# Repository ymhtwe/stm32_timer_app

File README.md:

# stm32_timer_app
general purpose control applications using stm32 timer module

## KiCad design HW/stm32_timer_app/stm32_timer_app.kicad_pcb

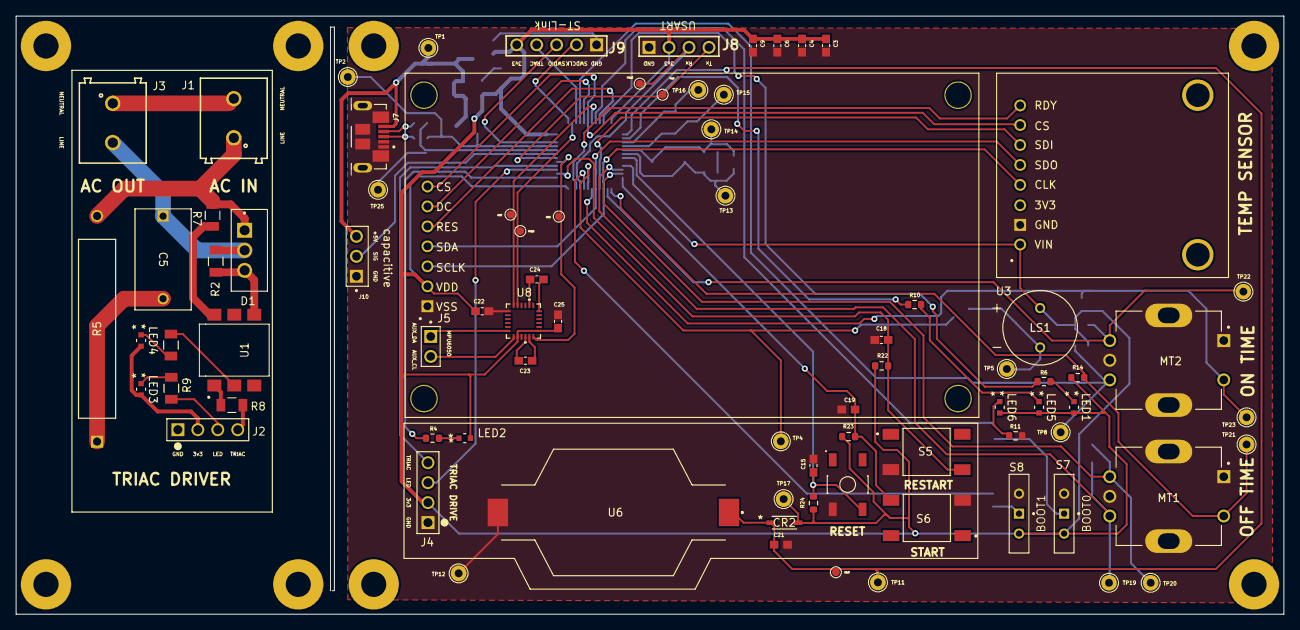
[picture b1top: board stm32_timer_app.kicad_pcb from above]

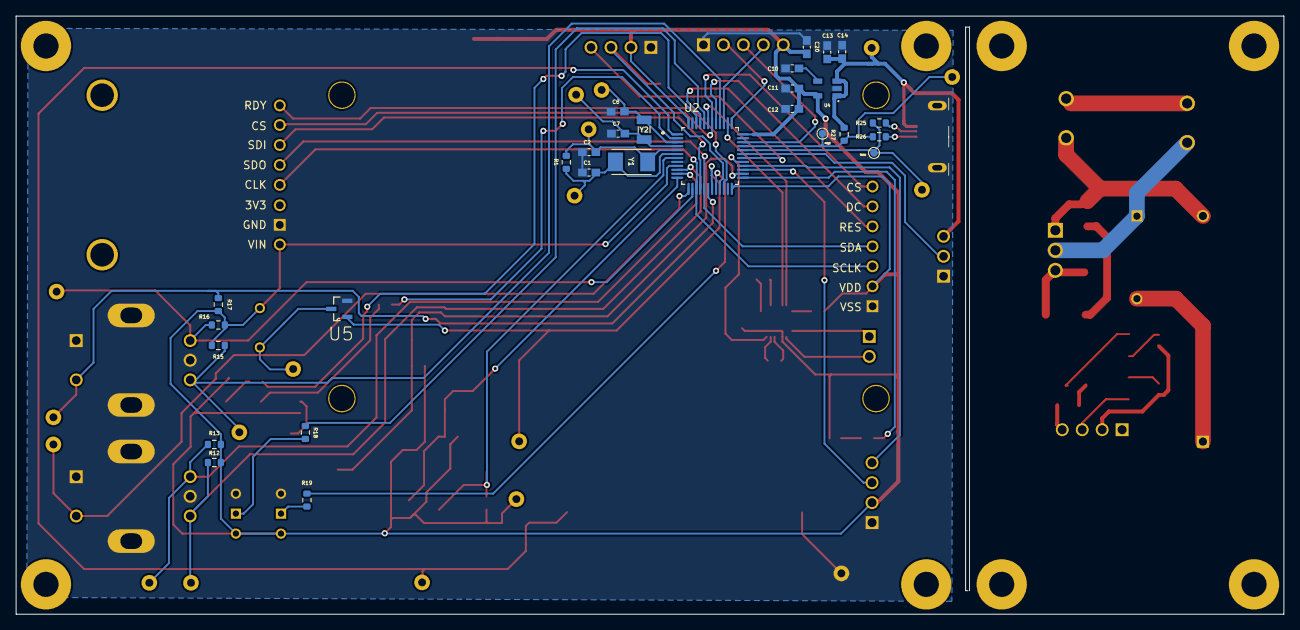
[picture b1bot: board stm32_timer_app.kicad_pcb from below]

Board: 2 copper layers, 161.3 x 76.1 mm, 101 parts (26 on the bottom side), 71 nets.

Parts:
C1, C2, C7, C8: 20p; CAPC1608X90
C3, C4, C6, C9, C12, C14, C20, C23, C25: 104; CAPC1608X90
C5: ECW-FD2J273KQ; CAP_ECWFD_FORMINGQ_12.6LX06.9TX09.9H_PAN
C10: 223; CAPC1608X90
C11: 106; CAPC1608X90
C13, C15, C18, C19: 105; CAPC1608X90
C21: LD03ZD475MAB2A; CAPC1608X90
C22, C24: 103; CAPC1608X90
CR2: 1N4148W-13-F; SOD123_DIO
D1: BTA16-600B; TO255P1040X460X1975-3
DS1: AOM12864A0-1.54WW-ANO; LCD_AOM12864A0-1.54WW-ANO
J1, J3: 691213710002
J2, J4: 61300411121; CONN_61300411121_WRE
J5: 54101-G0502LF; AMPHENOL_54101-G0502LF
J7: 105164-0001; MOLEX_105164-0001
J8: PH1RB-04-UA; HDRRA4W64P0X254_1X4_1016X250X850P
J9: PH1RB-05-UA_TEMP.; HDRRA5W64P0X254_1X5_1270X250X288P
J10: 75160-196-03LF; AMPHENOL_75160-196-03LF
LED1, LED2, LED3, LED4, LED5, LED6: 150060GS75000; LED_150060GS75000_WRE
LS1: AI-1027-TWT-3V-R; XDCR_AI-1027-TWT-3V-R
MT1, MT2: PEC11R-4215F-S0024; XDCR_PEC11R-4215F-S0024
R1, R25, R26, R27: 20R; R_0603_1608Metric
R2, R7, R9, R20: 330; RC1206N_YAG
R4, R6, R10, R11, R22, R23, R24: 330; R_0603_1608Metric
R5: 39; RES_OY_OHM
R8: 1k; RC1206N_YAG
R12, R13, R14, R15, R16, R17: 10K; R_0603_1608Metric
R18, R19: 100K; R_0603_1608Metric
S4: TL3342F160QG; SW_TL3342F160QG
S5, S6: 1571527-1; SW_1571527-1
S7, S8: MSS-102559-14A-D; SW_MSS-102559-14A-D
TP1, TP2, TP4, TP5, TP8, TP11, TP12, TP13, TP14, TP15, TP16, TP17, TP19, TP20, TP21, TP22, TP23, TP25: TestPoint_Probe; TestPoint_THTPad_D2.0mm_Drill1.0mm
U1: MOC3041SM; OPTO_MOC3041SM
U2: STM32F303C8T6; QFP50P900X900X160-48N
U3: MAX31865 AMPLIFIER; MAX31865
U4: RT9193-33GB; SOT94P279X129-5N
U5: MMBT2222A-7-F; SOT103P240X110-3N
U6: SMTU2032-LF; SMTU2032LF
U8: MPU-6050; QFN24_4X4X0P9_IVS
Y1: ABM3-8.000MHZ-J4Q-T; XTAL_ABM3-8.000MHZ-J4Q-T
Y2: ABS07-32.768KHZ-T; XTAL_ABS07-32.768KHZ-T

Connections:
/+3.3V: C3.1, C4.1, C6.1, C9.1, C11.2, C12.2, C20.1, C22.2, C25.1, CR2.2, DS1.2 (VCC), J4.2, J8.2, J9.5, LED1.2, LED2.2, LED5.2, LED6.2, LS1.P, R12.2, R13.2, R14.2, R15.2, R16.2, R17.2, R22.2, R23.2, R24.2, S7.2, S8.2, TP17.1, U2.9 (VDDA), U2.24 (VDD_1), U2.36 (VDD_2), U2.48 (VDD_3), U3.1 (VIN), U4.5 (VOUT), U8.8 (VLOGIC), U8.13 (VDD)
/+3.3VT: J2.2, LED3.2, LED4.2
/+5V: C13.2, C14.2, J7.5 (Vbus), J10.3, R27.1, TP1.1, U4.1 (VIN), U4.3 (EN)
/AUX_CL: J5.A2, U8.7 (AUX_CL)
/AUX_DA: J5.A1, U8.6 (AUX_DA)
/BOOT0: R18.2, U2.44 (BOOT0)
/BOOT1: R19.2, U2.20 (PB2)
/LED: J2.3, R9.1
/OSCIN: C2.2, R1.1, TP14.1, U2.5 (PF0/OSC_IN), Y1.1
/OSCOUT: C1.2, R1.2, TP13.1, U2.6 (PF1/OSC_OUT), Y1.2
/PA0: MT1.B, R12.1, TP19.1, U2.10 (PA0)
/PA1: MT1.A, R13.1, TP20.1, U2.11 (PA1)
/PA2: C19.1, R23.1, S6.4, U2.12 (PA2)
/PA3: MT1.2, R14.1, TP21.1, U2.13 (PA3)
/PA4: MT2.A, R16.1, TP22.1, U2.14 (PA4)
/PA5: DS1.3 (SCK), U2.15 (PA5), U3.4 (CLK)
/PA6: U2.16 (PA6), U3.6 (SDI)
/PA7: DS1.4 (SDA), U2.17 (PA7), U3.5 (SDO)
/PA8: U2.29 (PA8), U8.12 (INT)
/PA9: J8.4, U2.30 (PA9)
/PA10: J10.2, U2.31 (PA10)
/PA11: R25.2, TP25.1, U2.32 (PA11)
/PA12: R26.2, R27.2, TP2.1, U2.33 (PA12)
/PA13: C18.1, R22.1, S5.4, U2.26 (PB13)
/PA15: U2.38 (PA15), U8.23 (SCL)
/PB0: MT2.2, R17.1, TP23.1, U2.18 (PB0)
/PB1: TP4.1, U2.19 (PB1), U5.1 (B)
/PB3: J9.4, U2.39 (PB3)
/PB4: MT2.B, R15.1, TP8.1, U2.40 (PB4)
/PB5: DS1.6 (DC), U2.41 (PB5)
/PB6: DS1.7 (CS), U2.42 (PB6), U3.7 (CS)
/PB7: U2.43 (PB7), U8.24 (SDA)
/PB8: DS1.5 (RES), U2.45 (PB8)
/PB9: R6.1, U2.46 (PB9)
/PB10: J8.3, U2.21 (PB10)
/PB11: U2.22 (PB11), U3.8 (RDY)
/PB12: R4.1, U2.25 (PB12)
/PB14: J4.3, U2.27 (PB14)
/PB15: J4.4, U2.28 (PB15)
/PC13: R10.1, U2.2 (PC13)
/PC14: C8.2, TP16.1, U2.3 (PC14/OSC32_IN), Y2.1
/PC15: C7.2, TP15.1, U2.4 (PC15/OSC32_OUT), Y2.2
/RESET: C15.1, R24.1, S4.4, U2.7 (NRST)
/SWDCLK: J9.2, U2.37 (PA14)
/SWDIO: J9.3, U2.34 (PA13)
/VBAT: C21.1, CR2.1, TP11.1, U2.1 (VBAT), U6.1 (+)
GND: C1.1, C2.1, C3.2, C4.2, C6.2, C7.1, C8.1, C9.2, C10.1, C11.1, C12.1, C13.1, C14.1, C15.2, C18.2, C19.2, C20.2, C21.2, C22.1, C25.2, DS1.1 (GND), J2.1, J4.1, J7.1 (G), J7.2 (ID), J7.SH1 (SHIELD), J7.SH2 (SHIELD), J7.SH3 (SHIELD), J7.SH4 (SHIELD), J7.SH5 (SHIELD), J7.SH6 (SHIELD), J8.1, J9.1, J10.1, MT1.1, MT1.COM, MT1.S1 (SHIELD), MT1.S2 (SHIELD), MT2.1, MT2.COM, MT2.S1 (SHIELD), MT2.S2 (SHIELD), R11.1, R20.1, S4.2, S5.3, S6.3, S7.3, S8.3, TP12.1, U1.2, U2.8 (VSSA/VREF-), U2.23 (VSS_1), U2.35 (VSS_2), U2.47 (VSS_3), U3.2 (GND), U4.2 (GND), U5.2 (E), U6.2 (-), U8.1 (CLKIN), U8.9 (AD0)
unnamed: C5.1, D1.2, J3.2, R2.2
unnamed: C5.2, R5.1
unnamed: D1.1, J1.1, R5.2, R7.1
unnamed: D1.3, R2.1, U1.4
unnamed: J1.2, J3.1
unnamed: J2.4, R8.2
unnamed: J7.3 (D+), R26.1
unnamed: J7.4 (D-), R25.1
unnamed: LED1.1, R6.2
unnamed: LED2.1, R4.2
unnamed: LED3.1, R9.2
unnamed: LED4.1, R20.2
unnamed: LED5.1, R10.2
unnamed: LED6.1, R11.2
unnamed: R7.2, U1.6
unnamed: R8.1, U1.1
unnamed: R18.1, S7.1
unnamed: R19.1, S8.1
unnamed: C10.2, U4.4 (BP)
unnamed: LS1.N, TP5.1, U5.3 (C)
unnamed: C24.1, U8.20 (CPOUT)
unnamed: C23.2, U8.11 (FSYNC)
unnamed: C24.2, U8.18 (GND)
unnamed: C23.1, U8.10 (REGOUT)

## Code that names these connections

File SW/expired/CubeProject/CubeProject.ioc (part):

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Mcu.Name=STM32F303C(6-8)Tx
Mcu.Package=LQFP48
Mcu.UserName=STM32F303C8Tx
PA0.Signal=S_TIM2_CH1_ETR
PA1.Signal=S_TIM2_CH2
PA10.GPIOParameters=GPIO_Label
PA10.GPIO_Label=CAPACITIVE_TOUCH
PA10.Signal=GPIO_Input
PA11.GPIOParameters=GPIO_Label
PA11.GPIO_Label=USB-
PA11.Signal=GPIO_Input
PA12.GPIOParameters=GPIO_Label
PA12.GPIO_Label=USB+
PA12.Signal=GPIO_Input
PA13.Mode=Trace_Asynchronous_SW
PA13.Signal=SYS_JTMS-SWDIO
PA14.Mode=Trace_Asynchronous_SW
PA14.Signal=SYS_JTCK-SWCLK
PA2.GPIOParameters=GPIO_Label
PA2.GPIO_Label=SW1
PA2.Signal=GPIO_Input
PA3.GPIOParameters=GPIO_Label
PA3.GPIO_Label=ENCODER1_SW
PA3.Signal=GPIO_Input
PA4.Signal=S_TIM3_CH2
PA5.Mode=Full_Duplex_Master
PA5.Signal=SPI1_SCK
PA6.Mode=Full_Duplex_Master
PA6.Signal=SPI1_MISO
PA7.Mode=Full_Duplex_Master
PA7.Signal=SPI1_MOSI
PA9.Mode=Asynchronous
PA9.Signal=USART1_TX
PB0.GPIOParameters=GPIO_Label
PB0.GPIO_Label=ENCODER2_SW
PB0.Signal=GPIO_Input
PB1.GPIOParameters=GPIO_Label
PB1.GPIO_Label=BUZZER
PB1.Signal=GPIO_Output
PB10.Signal=GPIO_Output
PB11.Signal=GPIO_Input
PB12.GPIOParameters=GPIO_Label
PB12.GPIO_Label=LED3
PB12.Signal=GPIO_Output
PB13.GPIOParameters=GPIO_Label
PB13.GPIO_Label=SW2
PB13.Signal=GPIO_Input
PB14.GPIOParameters=GPIO_Label
PB14.GPIO_Label=TRIAC_LED
PB14.Signal=GPIO_Output
PB15.GPIOParameters=GPIO_Label
PB15.GPIO_Label=TRIAC_TRIG
PB15.Signal=GPIO_Output
PB2.Signal=SharedAnalog_PB2
PB3.Mode=Trace_Asynchronous_SW
PB3.Signal=SYS_JTDO-TRACESWO
PB4.Signal=S_TIM3_CH1
PB5.GPIOParameters=GPIO_Label
PB5.GPIO_Label=OLED_DC
PB5.Signal=GPIO_Output
PB6.Signal=GPIO_Output
PB7.Mode=Asynchronous
PB7.Signal=USART1_RX
PB8.GPIOParameters=GPIO_Label
PB8.GPIO_Label=OLED_RESET
PB8.Signal=GPIO_Output
PB9.GPIOParameters=GPIO_Label
PB9.GPIO_Label=LED2
PB9.Signal=GPIO_Output
PC13.GPIOParameters=GPIO_Label
PC13.GPIO_Label=LED1
PC13.Signal=GPIO_Output
PC14\ /\ OSC32_IN.Mode=LSE-External-Oscillator
PC14\ /\ OSC32_IN.Signal=RCC_OSC32_IN
PC15\ /\ OSC32_OUT.Mode=LSE-External-Oscillator
PC15\ /\ OSC32_OUT.Signal=RCC_OSC32_OUT
PF0\ /\ OSC_IN.Mode=HSE-External-Oscillator
PF0\ /\ OSC_IN.Signal=RCC_OSC_IN
PF1\ /\ OSC_OUT.Mode=HSE-External-Oscillator
PF1\ /\ OSC_OUT.Signal=RCC_OSC_OUT
RCC.HSEPLLFreq_Value=8000000
RCC.SYSCLKFreq_VALUE=72000000
RCC.SYSCLKSourceVirtual=RCC_SYSCLKSOURCE_PLLCLK
board=custom

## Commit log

2023-12-11 Create Temp Control Timer.pdf
    draft idea
2023-12-11 Create README.md
    stm32 timer module
2023-12-11 KiCad PCB Project
    creating blank PCB project file
2023-12-16 schematic design
    schematic design
2023-12-16 schematic design
    added schematic for 3v3 regulator, reset switch, micro USB and two led
2023-12-17 schematic design
    schematic design revision 1
2023-12-20 replace 16x2 lcd with 2.4" OLED foot print
    replace 16x2 lcd with 2.4" OLED foot print
2023-12-21 update schematic
    update schematic and foot print / 3D body libraries
2023-12-25 schematic
2023-12-28 schematic update
    mcu changed
2024-01-13 final schematic
2024-01-28 final PCB
    Final PCB
2024-03-02 normal updates
